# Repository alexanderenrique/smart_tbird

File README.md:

# smart_tbird

Electronics for the [1968 Thunderbird restomod](https://denton.works/wrenching/thunderbird-restomod/) — sensor nodes, in-dash display, alternator delay, programming tooling, and more.

**Website:** [denton.works/microelectronics/T-bird_electronics](https://denton.works/microelectronics/T-bird_electronics/)

## Projects

| Directory | Description |
|-----------|-------------|
| [`alternator_555_timer/`](alternator_555_timer/) | Analog 555 delay for alternator field excitation — [project page](https://denton.works/projects/alternator-555-timer/) |
| [`ESP32_UDPI_Programmer/`](ESP32_UDPI_Programmer/) | ESP32 + Python CLI UPDI programmer for ATtiny3216 — [work log](https://denton.works/microelectronics/ESP32_UPDI_Programmer/) |
| [`temp_fan_node/`](temp_fan_node/) | Engine sensing node PCB (temps, voltage, fan PWM, RS-485) |
| [`display/`](display/) | In-dash display node firmware and hardware |
| [`temp_fan/`](temp_fan/) | Earlier temp/fan PCB and code |

Active development is on the `platformIO` branch.

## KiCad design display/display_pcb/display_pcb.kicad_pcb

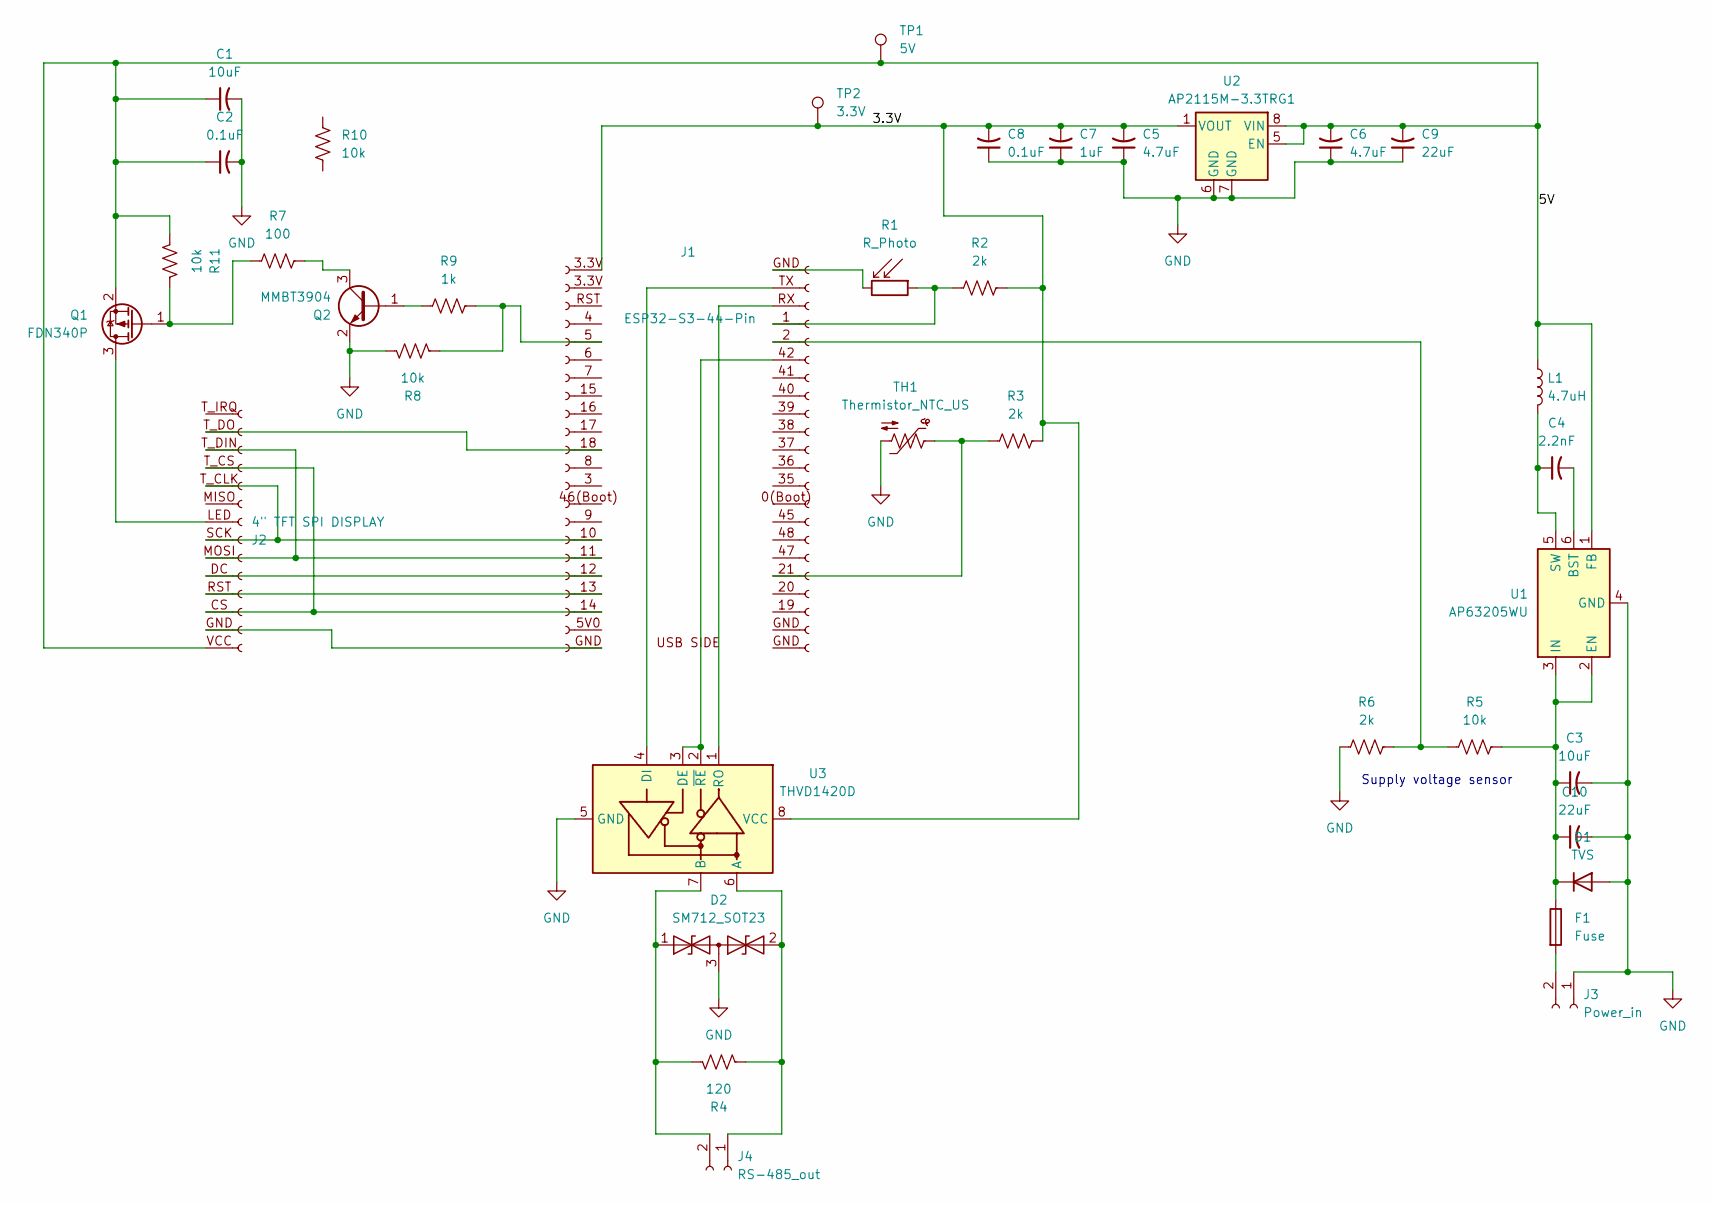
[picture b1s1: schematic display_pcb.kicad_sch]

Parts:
C1, C3: 10uF; C_1206_3216Metric_Pad1.33x1.80mm_HandSolder
C2, C8: 0.1uF; C_1206_3216Metric_Pad1.33x1.80mm_HandSolder
C4: 2.2nF; C_1206_3216Metric_Pad1.33x1.80mm_HandSolder
C5, C6: 4.7uF; C_1206_3216Metric_Pad1.33x1.80mm_HandSolder
C7: 1uF; C_1206_3216Metric_Pad1.33x1.80mm_HandSolder
C9, C10: 22uF; C_1206_3216Metric_Pad1.33x1.80mm_HandSolder
D1: TVS; D_SMB_Handsoldering
D2: SM712_SOT23; SOT-23
F1: Fuse; Fuseholder_Blade_Mini_Keystone_3568
J1: ESP32-S3-44-Pin; PinHeader_1x22_P2.54mm_Vertical
J2: 4" TFT SPI DISPLAY; PinHeader_1x14_P2.54mm_Vertical
J3: Power_in; Alex_2pin_65thou
J4: RS-485_out; Alex_2pin_65thou
L1: 4.7uH; L_1008_2520Metric_Pad1.43x2.20mm_HandSolder
Q1: FDN340P; SOT-23
Q2: MMBT3904; SOT-23
R1: R_Photo; Alex_2pin_65thou
R2, R3, R6: 2k; R_1206_3216Metric_Pad1.30x1.75mm_HandSolder
R4: 120; R_1206_3216Metric_Pad1.30x1.75mm_HandSolder
R5, R8, R10, R11: 10k; R_1206_3216Metric_Pad1.30x1.75mm_HandSolder
R7: 100; R_1206_3216Metric_Pad1.30x1.75mm_HandSolder
R9: 1k; R_1206_3216Metric_Pad1.30x1.75mm_HandSolder
TH1: Thermistor_NTC_US; R_1206_3216Metric_Pad1.30x1.75mm_HandSolder
TP1: 5V; TestPoint_Pad_2.5x2.5mm
TP2: 3.3V; TestPoint_Pad_2.5x2.5mm
U1: AP63205WU; TSOT-23-6
U2: AP2115M-3.3TRG1; SOIC-8_5.3x5.3mm_P1.27mm
U3: THVD1420D; SOIC-8_3.9x4.9mm_P1.27mm

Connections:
/3.3V: C5.2, C7.2, C8.2, J1.3.3V (Pin_15), R2.2, R3.1, TP2.1 (1_1), U2.1 (VOUT), U3.8 (VCC)
/5V: C1.1, C2.1, C6.2, C9.2, J2.VCC (Pin_1), L1.1, Q1.2 (S), R11.1, TP1.1 (1_1), U1.1 (FB), U2.5 (EN), U2.8 (VIN)
GND: C1.2, C2.2, C3.2, C5.1, C6.1, C7.1, C8.1, C9.1, C10.2, D1.2 (A), D2.3 (common), J3.1, Q2.2 (E), R6.1, R8.2, TH1.2, U1.4 (GND), U2.6 (GND), U2.7 (GND), U3.5 (GND)
unnamed: C3.1, C10.1, D1.1 (K), F1.1, R5.2, U1.2 (EN), U1.3 (IN)
unnamed: D2.1 (A1), J4.2, R4.1, U3.7 (B)
unnamed: D2.2 (A2), J4.1, R4.2, U3.6 (A)
unnamed: J1.21 (Pin_4), R3.2, TH1.1
unnamed: J1.18 (Pin_5), J2.T_DO
unnamed: J1.2 (Pin_11), R5.1, R6.2
unnamed: J1.5 (Pin_11), R8.1, R9.2
unnamed: J1.1 (Pin_12), R1.1, R2.1
unnamed: J1.14 (Pin_2), J2.CS (Pin_3), J2.T_CS
unnamed: J1.13 (Pin_3), J2.RST (Pin_4)
unnamed: J1.12 (Pin_4), J2.DC (Pin_5)
unnamed: J2.LED (Pin_8), Q1.3 (D)
unnamed: J1.10 (Pin_6), J2.SCK (Pin_7), J2.T_CLK (Pin_10)
unnamed: J1.11 (Pin_5), J2.MOSI (Pin_6), J2.T_DIN (Pin_12)
unnamed: F1.2, J3.2
unnamed: Q1.1 (G), R7.2, R11.2
unnamed: Q2.1 (B), R9.1
unnamed: Q2.3 (C), R7.1
unnamed: C4.2, U1.6 (BST)
unnamed: C4.1, L1.2, U1.5 (SW)
unnamed: J1.42 (Pin_10), U3.2 (~RE), U3.3 (DE)
unnamed: J1.TX (36), U3.4 (DI)
unnamed: J1.RX (Pin_13), U3.1 (RO)

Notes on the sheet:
Supply voltage sensor

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
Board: 2 copper layers, 37 parts (6 on the bottom side), 27 nets, no tracks yet.

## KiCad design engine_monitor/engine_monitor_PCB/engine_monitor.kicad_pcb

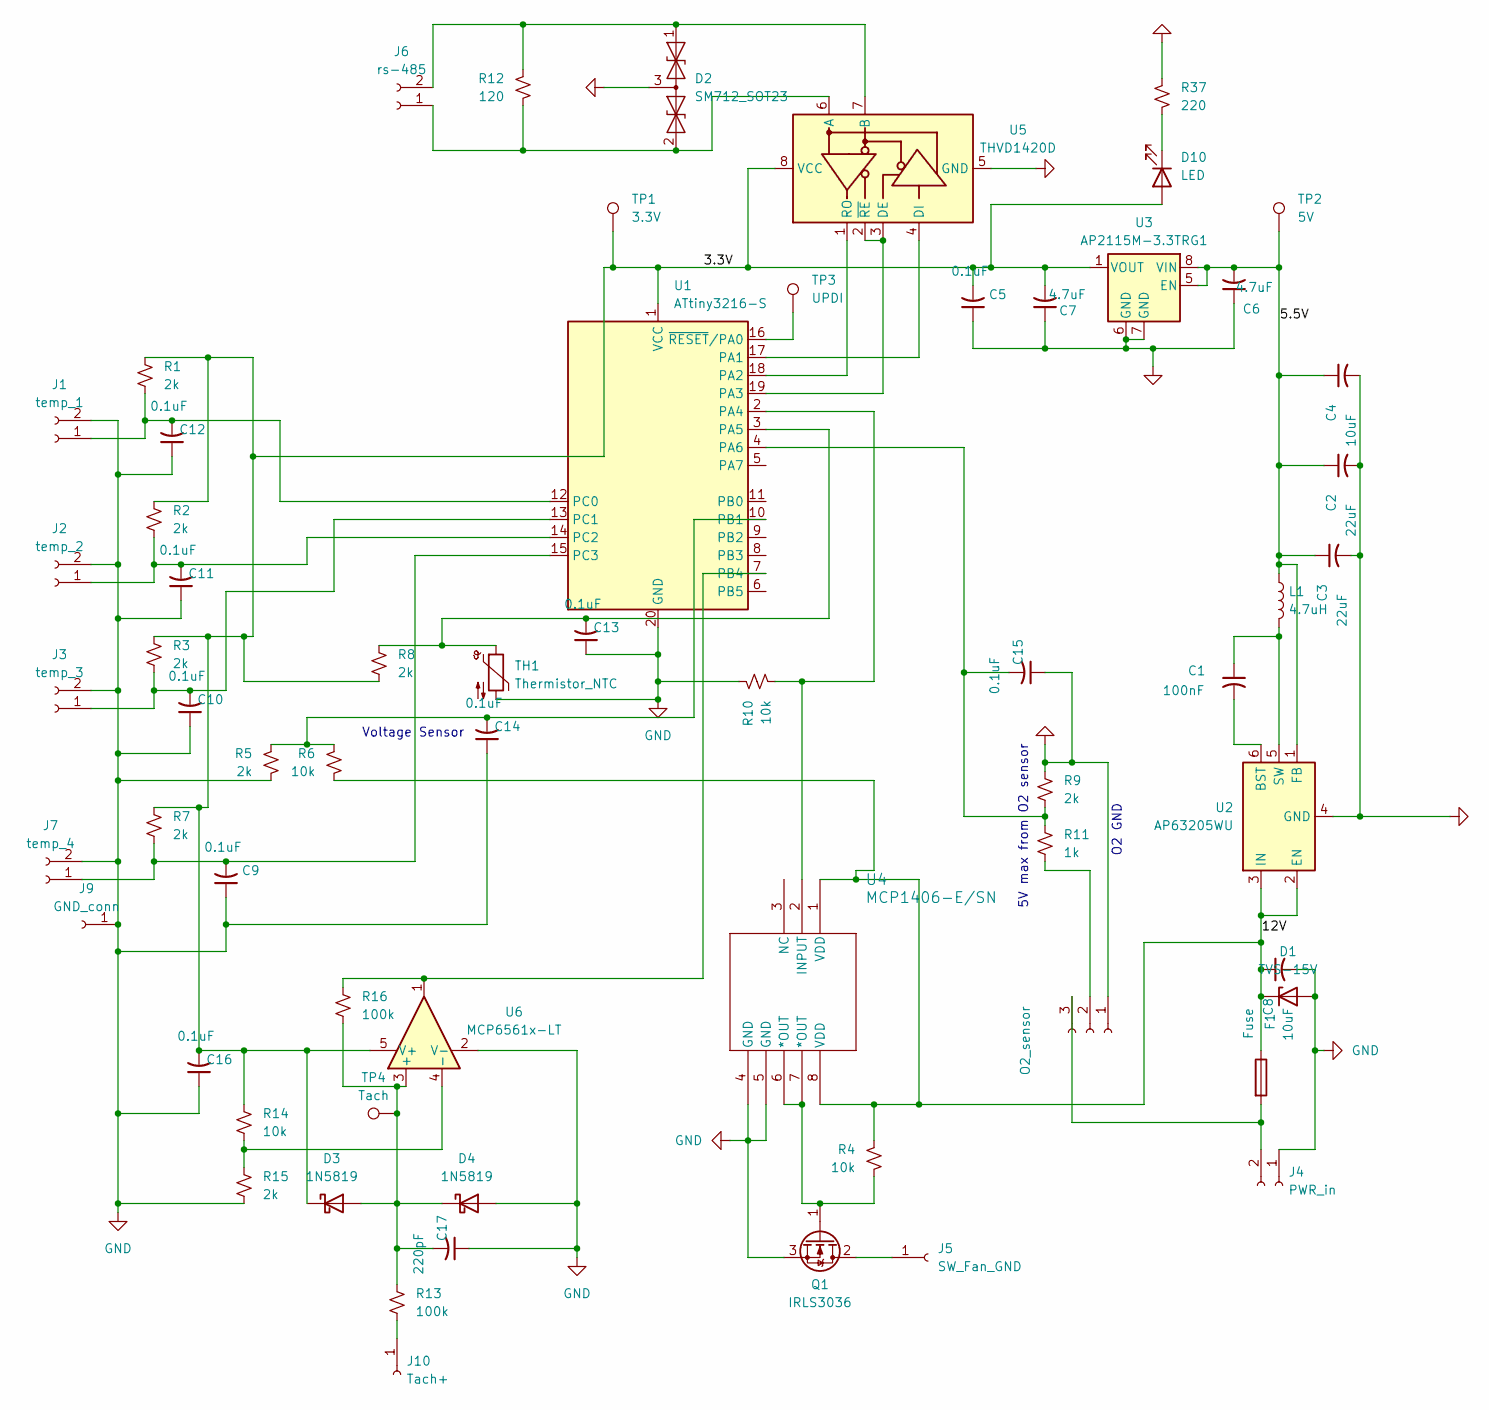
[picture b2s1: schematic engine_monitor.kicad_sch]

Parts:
C1: 100nF; C_1206_3216Metric_Pad1.33x1.80mm_HandSolder
C2, C3: 22uF; C_1206_3216Metric_Pad1.33x1.80mm_HandSolder
C4, C8: 10uF; C_1206_3216Metric_Pad1.33x1.80mm_HandSolder
C5, C9, C10, C11, C12, C13, C14, C15, C16: 0.1uF; C_1206_3216Metric_Pad1.33x1.80mm_HandSolder
C6, C7: 4.7uF; C_1206_3216Metric_Pad1.33x1.80mm_HandSolder
C17: 220pF; C_1206_3216Metric_Pad1.33x1.80mm_HandSolder
D1: TVS-15V; D_SMB_Handsoldering
D2: SM712_SOT23; SOT-23
D3, D4: 1N5819; D_SOD-123
D10: LED; LED_D3.0mm
F1: Fuse; Fuseholder_Blade_Mini_Keystone_3568
J1: temp_1; Alex_35thou_wire_hole
J2: temp_2; Alex_35thou_wire_hole
J3: temp_3; Alex_35thou_wire_hole
J4: PWR_in; PinHeader_2x01_P2.54mm_Vertical
J5: SW_Fan_GND; PinHeader_1x01_P1.00mm_Vertical
J6: rs-485; PinHeader_2x01_P2.54mm_Vertical
J7: temp_4; Alex_35thou_wire_hole
J8: O2_sensor; PinSocket_1x03_P1.00mm_Vertical
J9: GND_conn; Alex_1pin_065thou
J10: Tach+; Alex_1pin_065thou
L1: 4.7uH; L_1008_2520Metric_Pad1.43x2.20mm_HandSolder
Q1: IRLS3036; TO-263-3_TabPin2
R1, R2, R3, R5, R7, R8, R9, R15: 2k; R_1206_3216Metric_Pad1.30x1.75mm_HandSolder
R4, R6, R10, R14: 10k; R_1206_3216Metric_Pad1.30x1.75mm_HandSolder
R11: 1k; R_1206_3216Metric_Pad1.30x1.75mm_HandSolder
R12: 120; R_1206_3216Metric_Pad1.30x1.75mm_HandSolder
R13, R16: 100k; R_1206_3216Metric_Pad1.30x1.75mm_HandSolder
R37: 220; R_1206_3216Metric_Pad1.30x1.75mm_HandSolder
TH1: Thermistor_NTC; R_1206_3216Metric_Pad1.30x1.75mm_HandSolder
TP1: 3.3V; TestPoint_Pad_2.5x2.5mm
TP2: 5V; TestPoint_Pad_2.5x2.5mm
TP3: UPDI; TestPoint_Pad_2.5x2.5mm
TP4: Tach; Alex_35thou_wire_hole
U1: ATtiny3216-S; SOIC-20W_7.5x12.8mm_P1.27mm
U2: AP63205WU; TSOT-23-6
U3: AP2115M-3.3TRG1; SOIC-8-1EP_3.9x4.9mm_P1.27mm_EP2.29x3mm
U4: MCP1406-E/SN; SOIC-8-1EP_3.9x4.9mm_P1.27mm_EP2.62x3.51mm
U5: THVD1420D; SOIC-8_3.9x4.9mm_P1.27mm
U6: MCP6561x-LT; SOT-23-5

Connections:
/3.3V: C5.2, C7.2, C16.2, D3.1 (K), D10.2 (A), R1.1, R2.1, R3.1, R7.1, R8.2, R14.1, TP1.1 (1_1), U1.1 (VCC), U3.1 (VOUT), U5.8 (VCC), U6.5 (V+)
/5.5V: C2.1, C3.1, C4.1, C6.2, L1.1, TP2.1 (1_1), U2.1 (FB), U3.5 (EN), U3.8 (VIN)
/12V: C8.1, D1.1 (K), F1.1, R4.1, R6.2, U2.2 (EN), U2.3 (IN), U4.1 (VDD), U4.8 (VDD)
GND: C2.2, C3.2, C4.2, C5.1, C6.1, C7.1, C8.2, C9.1, C10.1, C11.1, C12.1, C13.1, C14.1, C15.1, C16.1, C17.1, D1.2 (A), D2.3 (common), D4.2 (A), J1.2, J2.2, J3.2, J4.1, J7.2, J8.1, J9.1 (Pin_1_1), Q1.3 (S), R5.2, R9.1, R10.1, R15.2, R37.1, TH1.2, U1.20 (GND), U2.4 (GND), U3.6 (GND), U3.7 (GND), U4.4 (GND), U4.5 (GND), U5.5 (GND), U6.2 (V-)
unnamed: D2.1 (A1), J6.2, R12.1, U5.7 (B)
unnamed: D2.2 (A2), J6.1, R12.2, U5.6 (A)
unnamed: C17.2, D3.2 (A), D4.1 (K), R13.1, R16.2, TP4.1 (1_1), U6.3 (+)
unnamed: D10.1 (K), R37.2
unnamed: C12.2, J1.1 (Pin_1_1), R1.2, U1.12 (PC0)
unnamed: C11.2, J2.1 (Pin_1_1), R2.2, U1.14 (PC2)
unnamed: C10.2, J3.1 (Pin_1_1), R3.2, U1.13 (PC1)
unnamed: F1.2, J4.2, J8.3
unnamed: J5.1 (Pin_1_1), Q1.2 (D)
unnamed: C9.2, J7.1 (Pin_1_1), R7.2, U1.15 (PC3)
unnamed: J8.2, R11.2
unnamed: J10.1 (Pin_1_1), R13.2
unnamed: Q1.1 (G), R4.2, U4.6 (*OUT), U4.7 (*OUT)
unnamed: U1.17 (PA1), U5.4 (DI)
unnamed: U1.18 (PA2), U5.1 (RO)
unnamed: U1.19 (PA3), U5.2 (~RE), U5.3 (DE)
unnamed: R10.2, U1.2 (PA4), U4.2 (INPUT)
unnamed: C13.2, R8.1, TH1.1, U1.3 (PA5)
unnamed: C15.2, R9.2, R11.1, U1.4 (PA6)
unnamed: C14.2, R5.1, R6.1, U1.10 (PB1)
unnamed: R16.1, U1.7 (PB4), U6.1
unnamed: TP3.1 (1_1), U1.16 (~RESET/PA0)
unnamed: C1.2, U2.6 (BST)
unnamed: C1.1, L1.2, U2.5 (SW)
unnamed: R14.2, R15.1, U6.4 (-)

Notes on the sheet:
Voltage Sensor
5V max from O2 sensor
O2 GND

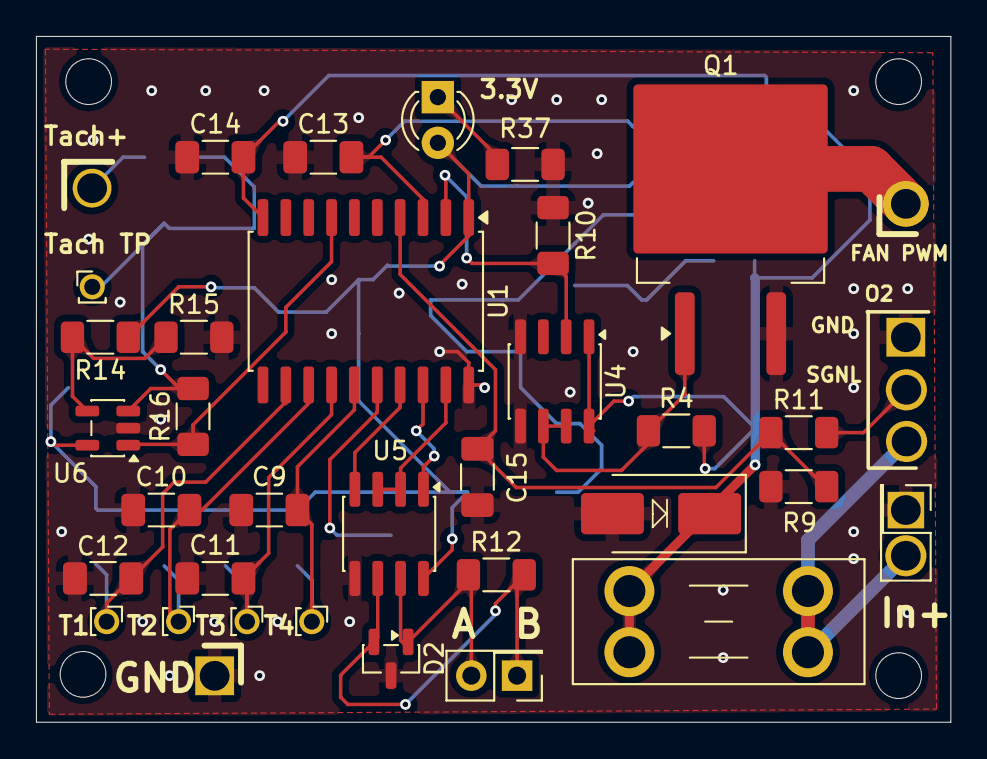
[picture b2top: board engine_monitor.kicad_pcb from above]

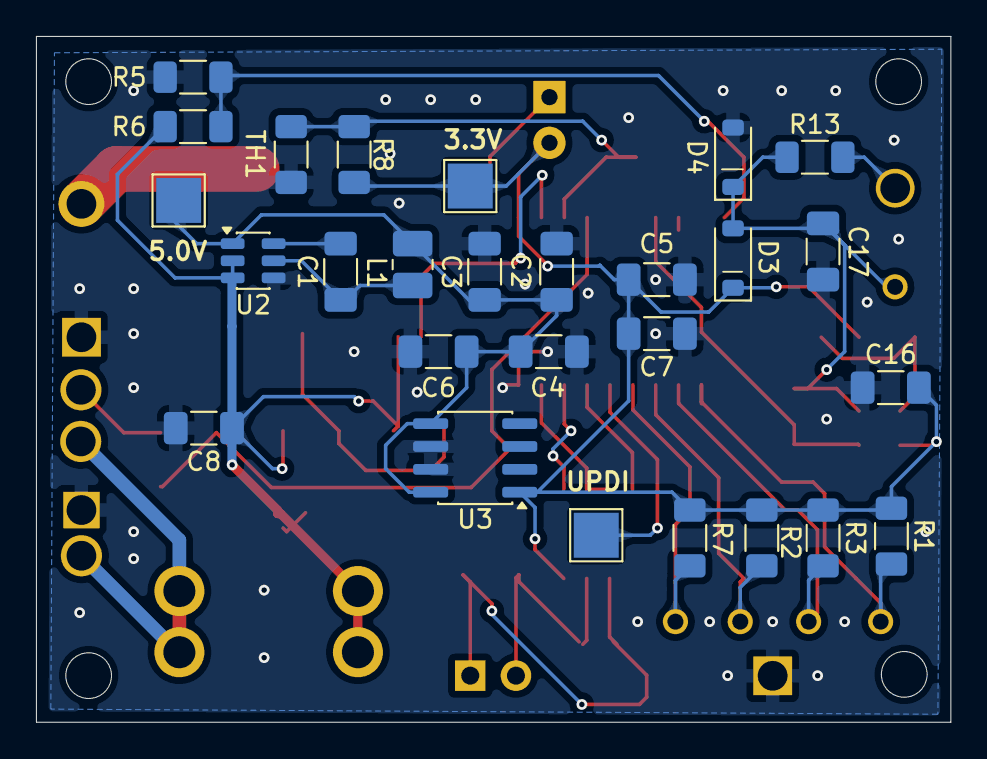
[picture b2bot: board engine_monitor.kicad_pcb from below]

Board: 2 copper layers, 50.8 x 38.1 mm, 63 parts (27 on the bottom side), 29 nets.

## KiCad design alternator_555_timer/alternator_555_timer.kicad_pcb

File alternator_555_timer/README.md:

# Alternator 555 Timer

A small analog delay board for classic cars with upgraded alternators. A CMOS 555 monostable holds the alternator field (I wire) off for ~10 seconds after key-on so V-belts can spin up before the load hits — no MCU, no firmware.

**Project page:** [denton.works/projects/alternator-555-timer](https://denton.works/projects/alternator-555-timer/)  
**Repository:** [github.com/alexanderenrique/smart_tbird](https://github.com/alexanderenrique/smart_tbird/tree/platformIO/alternator_555_timer)

## What's here

- KiCad schematic and PCB (`555_I_delay.kicad_*`)
- `BOM.csv` — bill of materials
- `555_v1.zip` — zipped gerbers and drill files for your PCB manufacturer

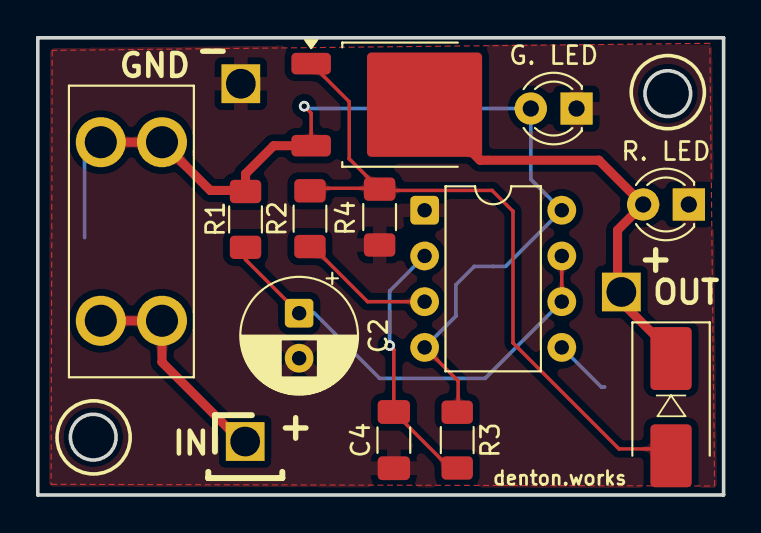
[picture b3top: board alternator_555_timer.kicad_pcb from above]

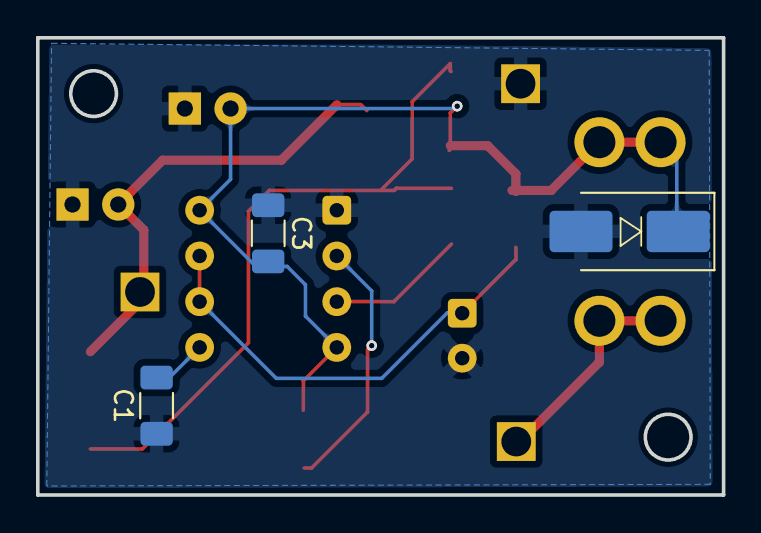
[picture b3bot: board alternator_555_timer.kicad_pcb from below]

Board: 2 copper layers, 38.1 x 25.4 mm, 18 parts (3 on the bottom side), 9 nets.

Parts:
C1, C3: 0.1uF; C_1206_3216Metric_Pad1.33x1.80mm_HandSolder
C2: 47uF; CP_Radial_D6.3mm_P2.50mm
C4: 1uF; C_1206_3216Metric_Pad1.33x1.80mm_HandSolder
D1, D2: SZ1SMB15AT3G; D_SMB_Handsoldering
D3: G. LED; LED_D3.0mm_Clear
D4: R. LED; LED_D3.0mm_Clear
F1: Fuse_Small; Fuseholder_Blade_Mini_Keystone_3568
J1: I_In; Alex_1pin_065thou
J2: I_out; Alex_1pin_065thou
J3: GND_Conn; Alex_1pin_065thou
Q1: FQD11P06TM; TO-252-2
R1: 220k; R_1206_3216Metric_Pad1.30x1.75mm_HandSolder
R2: 100; R_1206_3216Metric_Pad1.30x1.75mm_HandSolder
R3: 10k; R_1206_3216Metric_Pad1.30x1.75mm_HandSolder
R4: 100k; R_1206_3216Metric_Pad1.30x1.75mm_HandSolder
U1: TLC555CP; DIP-8_W7.62mm

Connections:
GND: C1.1, C2.2, C3.1, C4.1, D2.2 (A), D3.1 (K), D4.1 (K), J3.1 (Pin_1_1), R4.2, U1.1 (GND)
unnamed: D1.2 (A), Q1.1 (G), R2.2, R4.1
unnamed: D1.1 (K), D4.2 (A), J2.1 (Pin_1_1), Q1.2 (D)
unnamed: C3.2, D2.1 (K), D3.2 (A), F1.2, Q1.3 (S), R1.1, R3.1, U1.4 (~RST), U1.8 (VCC)
unnamed: F1.1, J1.1 (Pin_1_1)
unnamed: C1.2, U1.5 (CONT)
unnamed: C2.1, R1.2, U1.6 (THRES), U1.7 (DISCH)
unnamed: R2.1, U1.3 (OUT)
unnamed: C4.2, R3.2, U1.2 (TRIG)

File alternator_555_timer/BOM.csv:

Reference,Qty,Value,Footprint,Description
"C1,C3,C4",3,0.1uF,Capacitor_SMD:C_0805_2012Metric_Pad1.18x1.45mm_HandSolder,"Pulls Trig to ground momenterily,Smoothing Capacitor,Smoothing capacitor"
C2,1,47uF,Capacitor_THT:CP_Radial_D8.0mm_P3.80mm,Electrolytic capcitor for RC timing circuit
"D1,D2",2,SZ1SMB15AT3G,Diode_SMD:D_SMB_Handsoldering,"Gate/Drain TVS protection,Supply voltage TVS"
D3,1,Green LED,LED_THT:LED_D3.0mm_Clear,Light emitting diode
D4,1,Red LED,LED_THT:LED_D3.0mm_Clear,Light emitting diode
F1,1,Fuse_Small,Fuse:Fuseholder_Blade_Mini_Keystone_3568,"Fuse, 10A"
J1,1,I_In,Connector_Pin:12_AWG_TH_Alex,Wire Mounting hole
J2,1,I_out,Connector_Pin:12_AWG_TH_Alex,"Generic connector, single row, 01x01, script generated"
J3,1,GND_Conn,Connector_Pin:12_AWG_TH_Alex,Chassis and circuit ground
Q1,1,FQD11P06TM,Package_TO_SOT_SMD:TO-252-2,"-27A Id, -60V Vds, QFET P-Channel MOSFET, TO-220"
R1,1,220k,Resistor_SMD:R_1206_3216Metric_Pad1.30x1.75mm_HandSolder,Resistor for RC timing circuit
R2,1,100,Resistor_SMD:R_1206_3216Metric_Pad1.30x1.75mm_HandSolder,Resistor to minimize line ringing
R3,1,10k,Resistor_SMD:R_1206_3216Metric_Pad1.30x1.75mm_HandSolder,Raises trig up after initial start
R4,1,100k,Resistor_SMD:R_1206_3216Metric_Pad1.30x1.75mm_HandSolder,MOSFET pull-down resistor
U1,1,TLC555CP,Package_DIP:DIP-8_W7.62mm,"CMOS 555 compatible, PDIP-8"

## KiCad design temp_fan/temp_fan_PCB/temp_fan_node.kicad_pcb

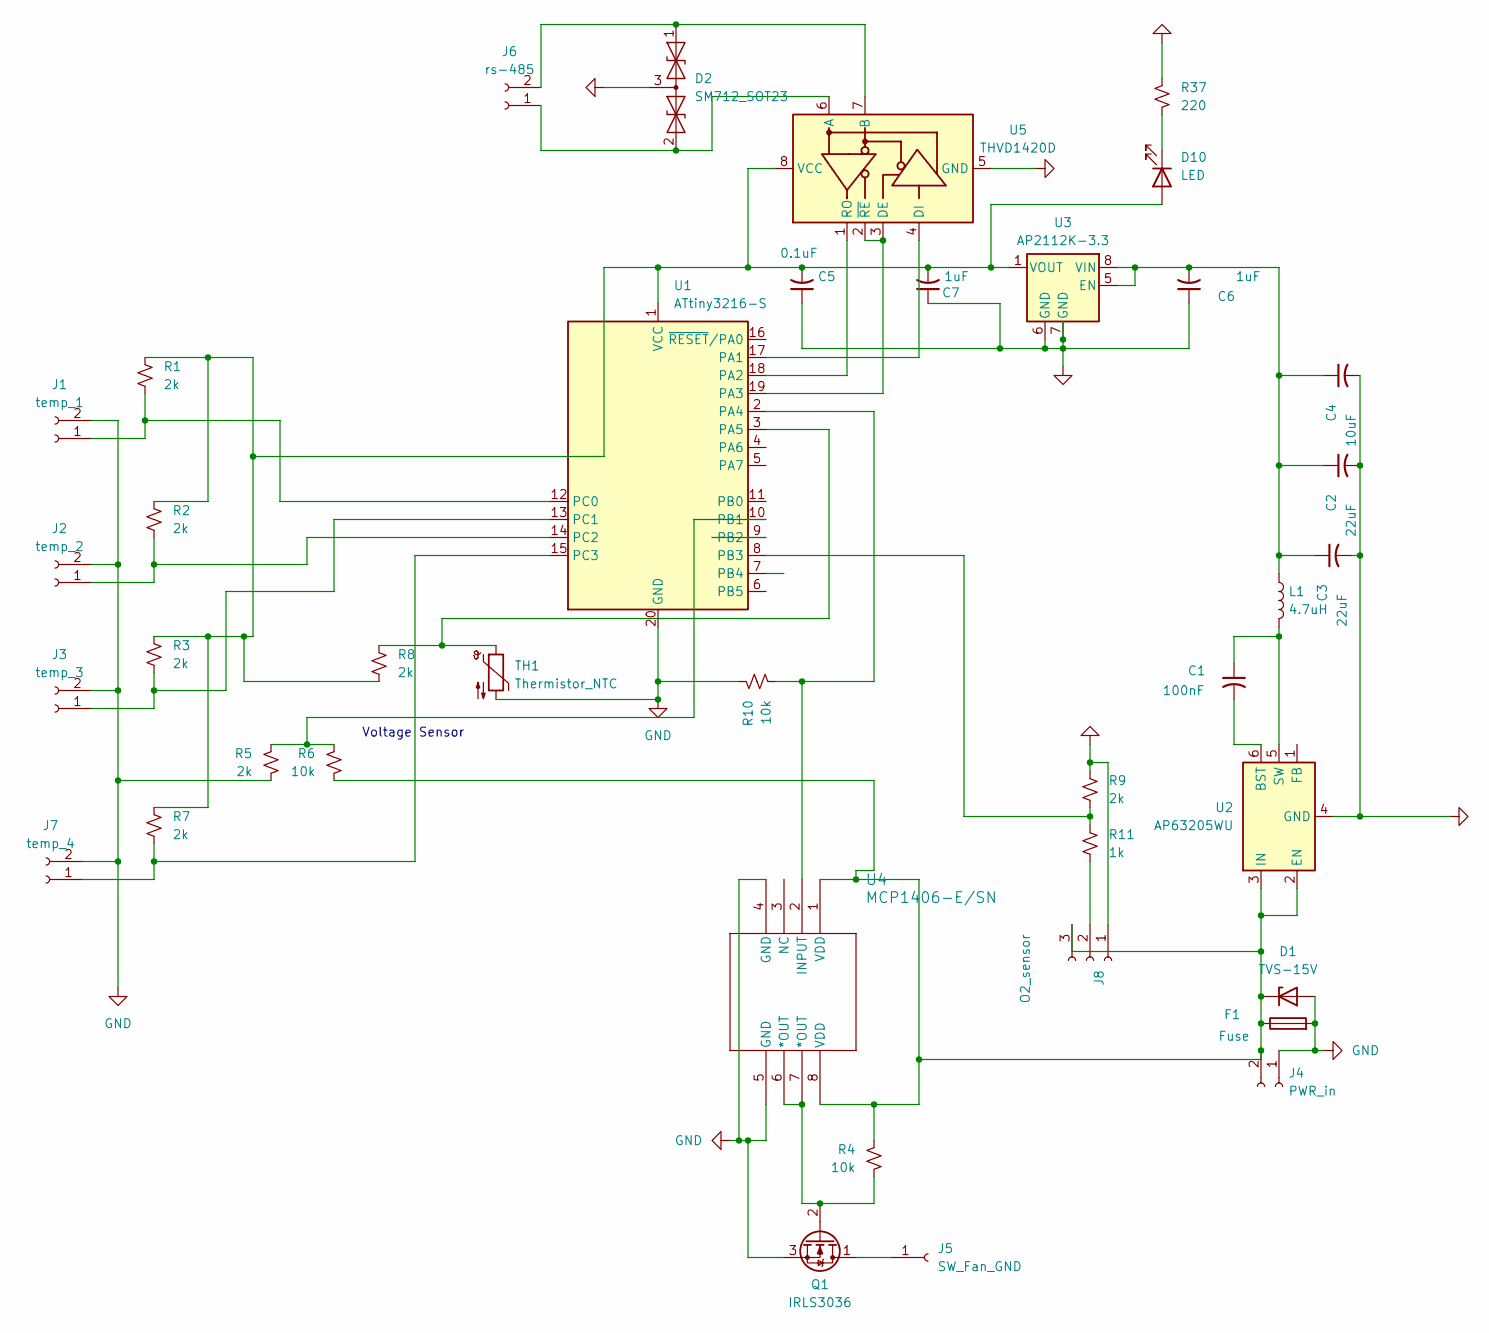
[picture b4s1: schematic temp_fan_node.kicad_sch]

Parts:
C1: 100nF; C_1206_3216Metric_Pad1.33x1.80mm_HandSolder
C2, C3: 22uF; C_1206_3216Metric_Pad1.33x1.80mm_HandSolder
C4: 10uF; C_1206_3216Metric_Pad1.33x1.80mm_HandSolder
C5: 0.1uF; C_1206_3216Metric_Pad1.33x1.80mm_HandSolder
C6, C7: 1uF; C_1206_3216Metric_Pad1.33x1.80mm_HandSolder
D1: TVS-15V; D_SMB_Handsoldering
D2: SM712_SOT23; SOT-23
D10: LED; LED_D3.0mm
F1: Fuse; Fuseholder_Blade_Mini_Keystone_3568
J1: temp_1; Alex_35thou_wire_hole
J2: temp_2; Alex_35thou_wire_hole
J3: temp_3; Alex_35thou_wire_hole
J4: PWR_in; PinHeader_2x01_P2.54mm_Vertical
J5: SW_Fan_GND; PinHeader_1x01_P1.00mm_Vertical
J6: rs-485; PinHeader_2x01_P2.54mm_Vertical
J7: temp_4; Alex_35thou_wire_hole
J8: O2_sensor; PinSocket_1x03_P1.00mm_Vertical
L1: 4.7uH; L_1008_2520Metric_Pad1.43x2.20mm_HandSolder
Q1: IRLS3036; TO-263-3_TabPin2
R1, R2, R3, R5, R7, R8, R9: 2k; R_1206_3216Metric_Pad1.30x1.75mm_HandSolder
R4, R6, R10: 10k; R_1206_3216Metric_Pad1.30x1.75mm_HandSolder
R11: 1k; R_1206_3216Metric_Pad1.30x1.75mm_HandSolder
R37: 220; R_1206_3216Metric_Pad1.30x1.75mm_HandSolder
TH1: Thermistor_NTC; R_1206_3216Metric_Pad1.30x1.75mm_HandSolder
U1: ATtiny3216-S; SOIC-20W_7.5x12.8mm_P1.27mm
U2: AP63205WU; TSOT-23-6
U3: AP2112K-3.3; SOIC-8-1EP_3.9x4.9mm_P1.27mm_EP2.29x3mm
U4: MCP1406-E/SN; SOIC-8-1EP_3.9x4.9mm_P1.27mm_EP2.62x3.51mm
U5: THVD1420D; SOIC-8_3.9x4.9mm_P1.27mm

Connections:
GND: C2.2, C3.2, C4.2, C5.1, C6.1, C7.1, D1.2 (A), D2.3 (common), F1.2, J1.2, J2.2, J3.2, J4.1, J7.2, J8.1, Q1.3 (S), R5.2, R9.1, R10.1, R37.1, TH1.2, U1.20 (GND), U2.4 (GND), U3.6 (GND), U3.7 (GND), U4.4 (GND), U4.5 (GND), U5.5 (GND)
unnamed: D1.1 (K), F1.1, J4.2, J8.3, R4.1, R6.2, U2.2 (EN), U2.3 (IN), U4.1 (VDD), U4.8 (VDD)
unnamed: D2.1 (A1), J6.2, U5.7 (B)
unnamed: D2.2 (A2), J6.1, U5.6 (A)
unnamed: C5.2, C7.2, D10.2 (A), R1.1, R2.1, R3.1, R7.1, R8.2, U1.1 (VCC), U3.1 (VOUT), U5.8 (VCC)
unnamed: D10.1 (K), R37.2
unnamed: J1.1 (Pin_1_1), R1.2, U1.12 (PC0)
unnamed: J2.1 (Pin_1_1), R2.2, U1.14 (PC2)
unnamed: J3.1 (Pin_1_1), R3.2, U1.13 (PC1)
unnamed: J5.1 (Pin_1_1), Q1.1 (D)
unnamed: J7.1 (Pin_1_1), R7.2, U1.15 (PC3)
unnamed: J8.2, R11.2
unnamed: Q1.2 (G), R4.2, U4.6 (*OUT), U4.7 (*OUT)
unnamed: U1.17 (PA1), U5.4 (DI)
unnamed: U1.18 (PA2), U5.1 (RO)
unnamed: U1.19 (PA3), U5.2 (~RE), U5.3 (DE)
unnamed: R10.2, U1.2 (PA4), U4.2 (INPUT)
unnamed: R8.1, TH1.1, U1.3 (PA5)
unnamed: R5.1, R6.1, U1.10 (PB1)
unnamed: R9.2, R11.1, U1.8 (PB3)
unnamed: C1.2, U2.6 (BST)
unnamed: C1.1, L1.2, U2.5 (SW)
unnamed: C2.1, C3.1, C4.1, C6.2, L1.1, U3.5 (EN), U3.8 (VIN)

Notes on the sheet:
Voltage Sensor

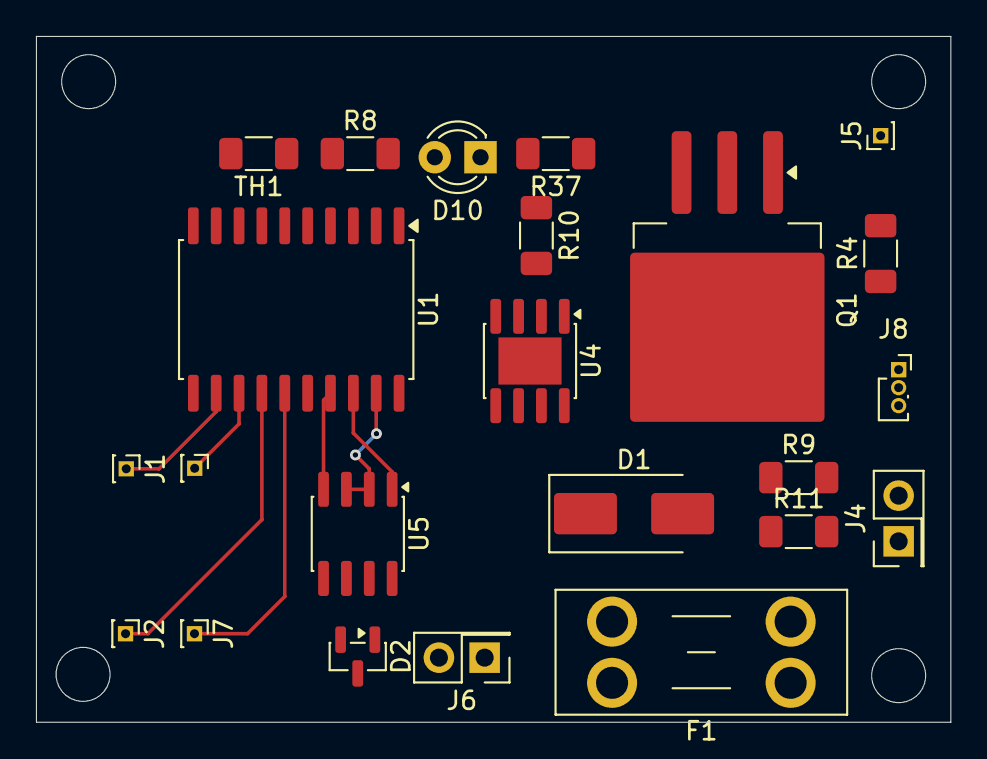
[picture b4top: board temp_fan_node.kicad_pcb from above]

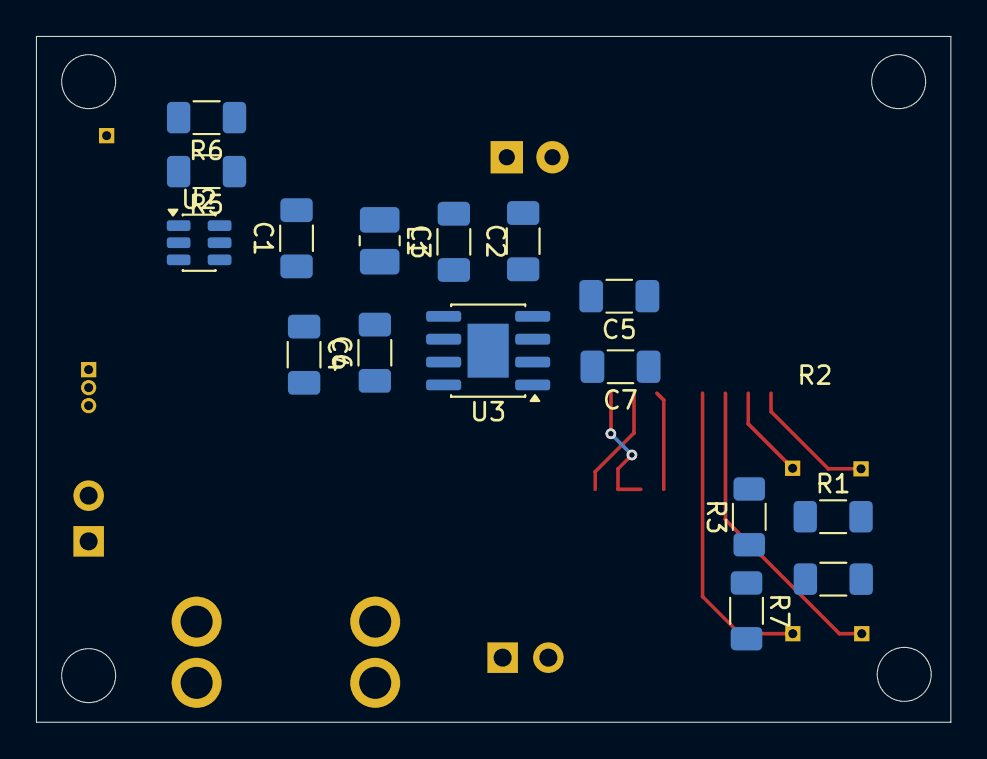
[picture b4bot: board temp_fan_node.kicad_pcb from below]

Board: 2 copper layers, 50.8 x 38.1 mm, 39 parts (16 on the bottom side), 23 nets.

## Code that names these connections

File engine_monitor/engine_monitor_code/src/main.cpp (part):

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#include <math.h>

namespace Pins {
constexpr uint8_t COOLANT_TEMP = PIN_PC0;
constexpr uint8_t OIL_TEMP = PIN_PC1;
constexpr uint8_t TRANS_TEMP = PIN_PC2;
constexpr uint8_t IAT_TEMP = PIN_PC3;
constexpr uint8_t PCB_TEMP = PIN_PA5;
constexpr uint8_t AFR = PIN_PA6;
constexpr uint8_t SYSTEM_VOLTAGE = PIN_PB1;
constexpr uint8_t RPM = PIN_PB4;
constexpr uint8_t FAN_PWM = PIN_PA4;
constexpr uint8_t MODBUS_DE_RE = PIN_PA3;
}  // namespace Pins

namespace Config {
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
    attachInterrupt(digitalPinToInterrupt(Pins::RPM), rpmEdgeHandler, RISING);

    // USART0 ALT1 routes TX to PA1 and RX to PA2.
    Serial.swap(1);
    Serial.begin(Config::MODBUS_BAUD);
}
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
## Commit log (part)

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2025-07-22 moved my platformIO project to the right directory so it'll push lol
2025-07-23 tried adding LVGL demo stuff, no joy
2025-07-23 still trying to get the demos working and understand this thing
2025-07-23 IT COMPILED
2025-07-24 troubleshooting code to the screentest
2025-07-25 made a simple button test, changed a lot of things in the config, hopefully that is why it is not reading the button
2025-07-29 GOT THE TOUCH WORKING ON LVGL
2025-07-29 Things are working well, done for the day
2025-07-30 added web server capabilities, temp test
2025-07-30 added offset to TMP36 sensor, included sht31 sensor to more accurately calibrate TMP36
2025-08-01 added SHT31 code, static IP addresses
2025-08-04 sht31 now also shows wifi strength, no DCHP, static IP
2025-08-17 converted from Wifi based to CAN based
2025-09-03 added a nodes folder, easier to keep track of each node and dependencies
2025-09-03 created a UI, added voltage sensing to central node
2025-09-04 changes to UI
2025-09-08 got the screen working again
2025-09-08 good working display, renamed it for clarity
2025-11-27 checkpoint thanksgiving morning
2025-11-29 working checkpoint
2025-11-30 added temp look up table
2025-12-02 untested engine bay cpp
2026-01-28 migration
2026-06-29 shout out oscilliscopes
2026-06-29 project progress
2026-06-29 layout for the day
2026-06-30 PCB updates
